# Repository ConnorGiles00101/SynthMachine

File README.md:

# SynthMachine
A set of Modular synthesizer modules designed around the SSI2130 VCO, SSI2140 Multi-Mode Filter, and the Daisy Seed Microcontroller.

Firmware requires a daisy seed build environment to compile, see daisy seed startup guide (https://daisy.audio/tutorials/cpp-dev-env/), requires updated libdaisy, daisysp, etc... to be cloned from relevant repos.

Very much a prototype.

Credit to timMJN and his Polymorph VCO module: https://github.com/TimMJN/Polymorph-VCO
His designs were helpful reference whilst learning modular synth i/o and standards regarding audio and CV voltage ranges and impedance.

VCO Machine and VCF Machine are designed to use the DAB2130 and DAB2140 breakout boards. As such they have DIP footprints instead of QFN, and do not have decoupling capacitors as they are already included on the breakout.

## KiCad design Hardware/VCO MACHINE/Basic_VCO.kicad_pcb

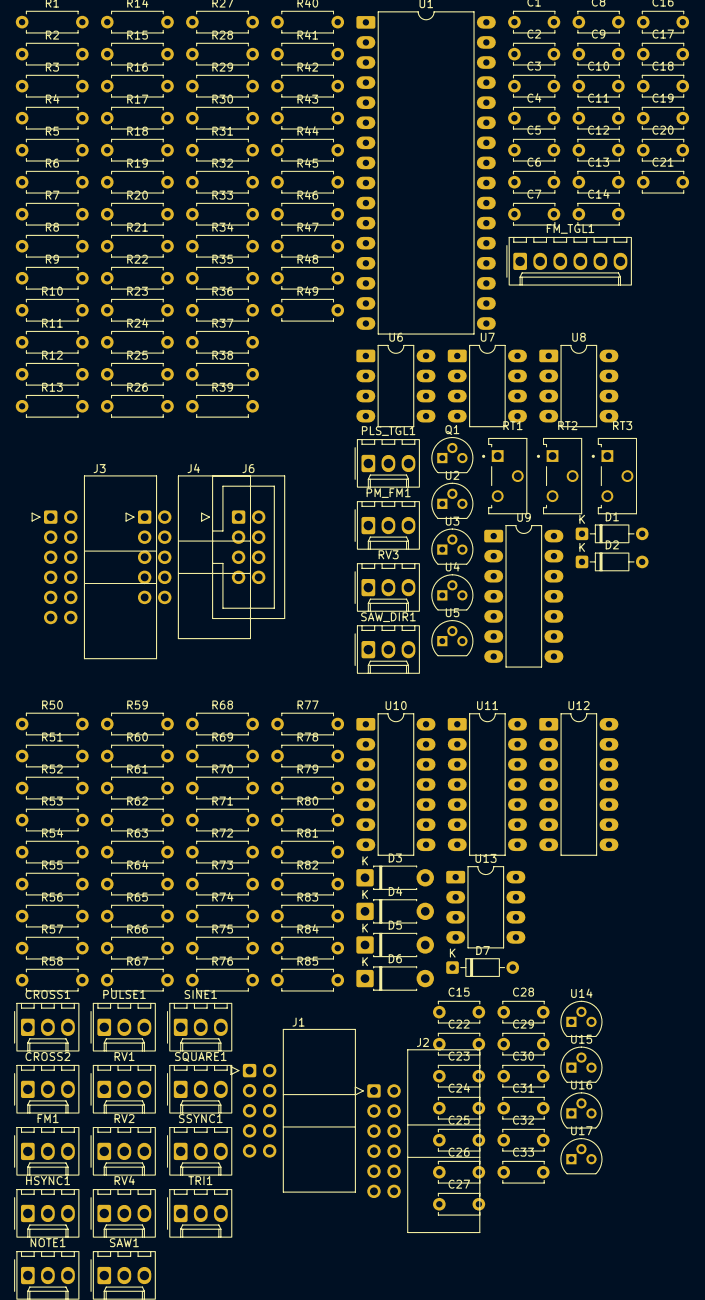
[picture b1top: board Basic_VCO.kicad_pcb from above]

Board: 4 copper layers, 170 parts (0 on the bottom side), 105 nets, no tracks yet.

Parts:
C1, C3, C30, C31: 0.33uF; C_Disc_D5.0mm_W2.5mm_P5.00mm
C2, C4, C12, C14, C16, C17, C18, C19, C20, C21, C22, C23, C24, C25, C26, C27, C28, C29, C32, C33: 0.1uF; C_Disc_D5.0mm_W2.5mm_P5.00mm
C5, C6, C8: 10nF; C_Disc_D5.0mm_W2.5mm_P5.00mm
C7: 3.9nF; C_Disc_D5.0mm_W2.5mm_P5.00mm
C9: 10uF; C_Disc_D5.0mm_W2.5mm_P5.00mm
C10, C11, C13, C15: 100pF; C_Disc_D5.0mm_W2.5mm_P5.00mm
CROSS1, CROSS2: AudioJack2_SwitchT; Molex_KK-254_AE-6410-03A_1x03_P2.54mm_Vertical
D1, D2, D7: 1N4148; D_DO-35_SOD27_P7.62mm_Horizontal
D3, D4, D5, D6: 1N5817; D_DO-41_SOD81_P7.62mm_Horizontal
FM1: AudioJack2_SwitchT; Molex_KK-254_AE-6410-03A_1x03_P2.54mm_Vertical
FM_TGL1: SW_DPDT_x2; Molex_KK-254_AE-6410-06A_1x06_P2.54mm_Vertical
HSYNC1: AudioJack2_SwitchT; Molex_KK-254_AE-6410-03A_1x03_P2.54mm_Vertical
J1, J4: Conn_02x05_Odd_Even; IDC-Header_2x05_P2.54mm_Horizontal
J2, J3: Conn_02x06_Odd_Even; IDC-Header_2x06_P2.54mm_Horizontal
J6: Conn_02x05_Odd_Even; IDC-Header_2x04_P2.54mm_Vertical
NOTE1: AudioJack2_SwitchT; Molex_KK-254_AE-6410-03A_1x03_P2.54mm_Vertical
PLS_TGL1: SW_SPDT; Molex_KK-254_AE-6410-03A_1x03_P2.54mm_Vertical
PM_FM1: SW_SPDT; Molex_KK-254_AE-6410-03A_1x03_P2.54mm_Vertical
PULSE1: AudioJack2_SwitchT; Molex_KK-254_AE-6410-03A_1x03_P2.54mm_Vertical
Q1: 2N7000; TO-92
R1, R3, R58, R83: 10; R_Axial_DIN0207_L6.3mm_D2.5mm_P7.62mm_Horizontal
R2, R4, R13, R84, R85: 267; R_Axial_DIN0207_L6.3mm_D2.5mm_P7.62mm_Horizontal
R5: 15k; R_Axial_DIN0207_L6.3mm_D2.5mm_P7.62mm_Horizontal
R6, R7, R10, R15, R26, R35, R37, R45, R47, R57, R59, R63, R67, R71, R75: 10k; R_Axial_DIN0207_L6.3mm_D2.5mm_P7.62mm_Horizontal
R8, R50, R51, R52, R53, R54, R55, R81, R82: 49.9k; R_Axial_DIN0207_L6.3mm_D2.5mm_P7.62mm_Horizontal
R9: 267k; R_Axial_DIN0207_L6.3mm_D2.5mm_P7.62mm_Horizontal
R11, R24, R25, R34: 100k; R_Axial_DIN0207_L6.3mm_D2.5mm_P7.62mm_Horizontal
R12: 22.1k; R_Axial_DIN0207_L6.3mm_D2.5mm_P7.62mm_Horizontal
R14, R16, R33: 100; R_Axial_DIN0207_L6.3mm_D2.5mm_P7.62mm_Horizontal
R17: 19.6k; R_Axial_DIN0207_L6.3mm_D2.5mm_P7.62mm_Horizontal
R18, R20: 4.75k; R_Axial_DIN0207_L6.3mm_D2.5mm_P7.62mm_Horizontal
R19: 4.02k; R_Axial_DIN0207_L6.3mm_D2.5mm_P7.62mm_Horizontal
R21: 12.7k; R_Axial_DIN0207_L6.3mm_D2.5mm_P7.62mm_Horizontal
R22, R23, R27, R28, R29, R30, R31, R32, R38, R39, R40, R41, R42, R43, R44, R46, R48, R49, R60, R64, R68, R72, R76, R78: 20k; R_Axial_DIN0207_L6.3mm_D2.5mm_P7.62mm_Horizontal
R36: 499k; R_Axial_DIN0207_L6.3mm_D2.5mm_P7.62mm_Horizontal
R56: 90.9k; R_Axial_DIN0207_L6.3mm_D2.5mm_P7.62mm_Horizontal
R61, R65, R69, R73: 40.2k; R_Axial_DIN0207_L6.3mm_D2.5mm_P7.62mm_Horizontal
R62, R66, R70, R74, R77, R79: 1k; R_Axial_DIN0207_L6.3mm_D2.5mm_P7.62mm_Horizontal
R80: 1M; R_Axial_DIN0207_L6.3mm_D2.5mm_P7.62mm_Horizontal
RT1, RT2, RT3: 5k; TRIM_PV36Y203C01B00
RV1, RV2, RV4: 100k; Molex_KK-254_AE-6410-03A_1x03_P2.54mm_Vertical
RV3: 5k; Molex_KK-254_AE-6410-03A_1x03_P2.54mm_Vertical
SAW1: AudioJack2_SwitchT; Molex_KK-254_AE-6410-03A_1x03_P2.54mm_Vertical
SAW_DIR1: SW_SPDT; Molex_KK-254_AE-6410-03A_1x03_P2.54mm_Vertical
SINE1: AudioJack2_SwitchT; Molex_KK-254_AE-6410-03A_1x03_P2.54mm_Vertical
SQUARE1: AudioJack2_SwitchT; Molex_KK-254_AE-6410-03A_1x03_P2.54mm_Vertical
SSYNC1: AudioJack2_SwitchT; Molex_KK-254_AE-6410-03A_1x03_P2.54mm_Vertical
TRI1: AudioJack2_SwitchT; Molex_KK-254_AE-6410-03A_1x03_P2.54mm_Vertical
U1: SSI2130; DIP-32_W15.24mm_LongPads
U2, U14: L78L05_TO92; TO-92
U3, U5, U16, U17: TL431LP; TO-92
U4, U15: L79L05_TO92; TO-92
U6, U7, U13: TL072; DIP-8_W7.62mm_LongPads
U8: LM311; DIP-8_W7.62mm_LongPads
U9, U10, U11, U12: TL074; DIP-14_W7.62mm_LongPads

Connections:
+2V5: D3.1 (K), D5.1 (K), FM_TGL1.1 (A), R2.2, R11.2, R12.1, R15.2, R21.2, R28.2, R84.2, RT1.3, U1.23 (VREF), U3.1 (REF), U3.3 (K), U16.1 (REF), U16.3 (K)
+5V: C2.1, C32.1, R2.1, R14.1, R22.2, R35.2, R84.1, RV2.3, SAW_DIR1.1 (A), U1.27 (V+), U2.1 (VO), U14.1 (VO)
+12V: C12.1, C17.1, C18.1, C20.1, C23.1, C24.1, C26.1, C28.1, J1.9, J1.10, J4.9, J4.10, R1.1, R58.1, U6.4 (V-), U7.4 (V-), U8.8 (V+), U9.11 (V-), U10.11 (V-), U11.11 (V-), U12.11 (V-), U13.8 (V+)
-1V0: R40.1, U6.1, U6.2 (-)
-2V5: R4.2, R5.1, R60.1, R64.1, R68.1, R72.1, R85.2, U5.2 (A), U17.2 (A)
-5V: C4.1, C33.1, R4.1, R85.1, U4.3 (VO), U15.3 (VO)
-12V: C14.2, C16.2, C19.2, C21.2, C22.2, C25.2, C27.2, C29.2, J1.1, J1.2, J4.1, J4.2, J6.1, J6.2, R3.1, R17.2, R83.1, U1.8 (V-), U6.8 (V+), U7.8 (V+), U8.4 (V-), U9.4 (V+), U10.4 (V+), U11.4 (V+), U12.4 (V+), U13.4 (V-)
CROSSFADE CV: J3.4, R37.1, R47.1
CROSSFADE IN: J2.4, U11.8, U11.9 (-)
GND: C1.2, C2.2, C3.2, C4.2, C7.2, C8.2, C12.2, C14.1, C16.1, C17.2, C18.2, C19.1, C20.2, C21.1, C22.1, C23.2, C24.2, C25.1, C26.2, C27.1, C28.2, C29.1, C30.2, C31.2, C32.2, C33.2, D4.2 (A), D6.2 (A), J1.3, J1.4, J1.5, J1.6, J1.7, J1.8, J2.2, J3.2, J4.3, J4.4, J4.5, J4.6, J4.7, J4.8, J6.3, J6.4, J6.5, J6.6, J6.7, J6.8, Q1.1 (S), R6.2, R7.1, R16.2, R18.2, R20.2, R23.1, R24.1, R25.1, R26.2, R33.1, R48.1, R51.2, R54.1, R57.1, R80.2, R82.2, RT1.1, RT2.1, RV1.1, RV2.1, RV4.1, SAW_DIR1.3 (C), U1.15 (DGND), U1.16 (AGND), U1.20 (HFT_BASE), U2.2 (GND), U3.2 (A), U4.1 (GND), U5.1 (REF), U5.3 (K), U6.5 (+), U7.3 (+), U8.1 (GND), U9.3 (+), U9.5 (+), U9.12 (+), U11.12 (+), U12.3 (+), U12.5 (+), U12.10 (+), U12.12 (+), U13.2 (-), U14.2 (GND), U15.1 (GND), U16.2 (A), U17.1 (REF), U17.3 (K)
HARD SYNC CV: C5.1, J3.6, R7.2
HARD SYNC IN: J2.6, U10.13 (-), U10.14
LIN FREQ IN: R36.2, U1.21 (LIN_FREQ)
MIX OUT: R26.1, U1.25 (MIX_OUT)
NOTE CV: J3.12, R8.1
NOTE IN: J2.12, U10.1, U10.2 (-)
unnamed: C8.1, R13.1
unnamed: C13.1, R34.2
unnamed: C15.2, R78.2, R79.1, U13.7
unnamed: D1.2 (A), D2.1 (K), U9.1
unnamed: D1.1 (K), R38.2, R39.1
unnamed: D2.2 (A), R41.2, R42.1
unnamed: D3.2 (A), D4.1 (K), R81.2, R82.1, U10.10 (+)
unnamed: D5.2 (A), D6.1 (K), R50.2, R51.1, U10.12 (+)
unnamed: D7.2 (A), U11.7
unnamed: D7.1 (K), RV4.3, U11.6 (-)
unnamed: FM_TGL1.2 (B), R36.1
unnamed: C11.2, FM_TGL1.3 (C), R32.2, U7.7
unnamed: FM_TGL1.4 (A), SAW_DIR1.2 (B)
unnamed: C13.2, FM_TGL1.6 (C), Q1.2 (G), R35.1, U8.7
unnamed: C9.2, PM_FM1.1 (A), R27.1
unnamed: C9.1, PM_FM1.3 (C)
unnamed: Q1.3 (D), R31.2, U7.5 (+)
unnamed: R9.1, RT2.2
unnamed: R10.1, RT1.2
unnamed: R12.2, RT3.2, RT3.3
unnamed: R14.2, R15.1, RV3.3
unnamed: R16.1, R17.1, RV3.1
unnamed: R43.2, R44.2, R45.2, U9.7
unnamed: R46.2, R49.1, U9.8
unnamed: R53.1, RV2.2
unnamed: R55.2, R56.1, U11.1
unnamed: R61.1, R62.2, U12.1
unnamed: R65.1, R66.2, U12.7
unnamed: R69.1, R70.2, U12.8
unnamed: R73.1, R74.2, U12.14
unnamed: R76.1, R77.2, U13.1
unnamed: R13.2, U1.26 (BW_COMP)
unnamed: R8.2, R9.2, R10.2, R11.1, U1.7 (EXPO_FREQ)
unnamed: RT3.1, U1.22 (EXPO_SCALE)
unnamed: C5.2, U1.17 (HARD_SYNC)
unnamed: RT2.3, U1.6 (HF_TRACK)
unnamed: C6.2, U1.19 (SOFT_SYNC)
unnamed: C7.1, U1.14 (TCAP)
unnamed: R18.1, R19.1, U1.2 (SINE_IN+)
unnamed: R20.1, R21.1, U1.3 (SINE_IN-)
unnamed: R24.2, U1.12 (AUX1_MIX)
unnamed: R25.2, U1.13 (AUX2_MIX)
unnamed: C1.1, R1.2, U2.3 (VI)
unnamed: C3.1, R3.2, U4.2 (VI)
unnamed: R5.2, R6.1, U6.3 (+)
unnamed: U6.6 (-), U6.7
unnamed: C10.1, R27.2, R28.1, R29.1, U7.2 (-)
unnamed: C11.1, R30.2, R32.1, U7.6 (-)
unnamed: R33.2, R34.1, U8.2 (+)
unnamed: C10.2, R29.2, R30.1, R31.1, U7.1, U8.3 (-)
unnamed: R37.2, R38.1, R40.2, R41.1, U9.2 (-)
unnamed: R42.2, R43.1, U9.6 (-)
unnamed: R47.2, R48.2, U9.10 (+)
unnamed: R45.1, R46.1, U9.9 (-)
unnamed: U9.13 (-), U9.14
unnamed: R80.1, U10.3 (+)
unnamed: RV1.2, U10.5 (+)
unnamed: R52.2, R53.2, U11.3 (+)
unnamed: R54.2, R55.1, U11.2 (-)
unnamed: R56.2, R57.2, U11.5 (+)
unnamed: RV4.2, U11.10 (+)
unnamed: U11.13 (-), U11.14
unnamed: R59.2, R60.2, R61.2, U12.2 (-)
unnamed: R63.2, R64.2, R65.2, U12.6 (-)
unnamed: R67.2, R68.2, R69.2, U12.9 (-)
unnamed: R71.2, R72.2, R73.2, U12.13 (-)
unnamed: R75.2, R76.2, U13.3 (+)
unnamed: C15.1, R78.1, U13.5 (+)
unnamed: C30.1, R58.2, U14.3 (VI)
unnamed: C31.1, R83.2, U15.2 (VI)
PM/FM CV: J3.10, PM_FM1.2 (B)
PM/FM IN: J2.10, U10.6 (-), U10.7
PULSE MIX: R44.1, U1.11 (PULSE_MIX)
PULSE OUT: J3.3, J3.7, U1.30 (PULSE_OUT)
PULSE WAVE: J2.3, J2.7, R71.1
PWM+: RV3.2, U1.32 (PWM+)
PWM-: PLS_TGL1.2 (B), U1.31 (PWM-)
SAW MIX: R49.2, U1.10 (SAW_MIX)
SAW OUT: J3.9, PLS_TGL1.3 (C), U1.29 (SAW_OUT)
SAW WAVE: J2.9, R63.1
SINE OUT: J3.1, U1.24 (SINE_OUT)
SINE WAVE: J2.1, R75.1
SOFT SYNC CV: C6.1, J3.8
SOFT SYNC IN: J2.8, U10.8, U10.9 (-)
SQUARE OUT: J3.5, R22.1, R23.2, U1.28 (SQUARE_OUT)
SQUARE WAVE: J2.5, R67.1
TIME REV IN: FM_TGL1.5 (B), U1.18 (TIME_REVERSE)
TRI MIX: R39.2, U1.9 (TRI_MIX)
TRI OUT: PLS_TGL1.1 (A), R19.2, U1.1 (TRI_OUT)

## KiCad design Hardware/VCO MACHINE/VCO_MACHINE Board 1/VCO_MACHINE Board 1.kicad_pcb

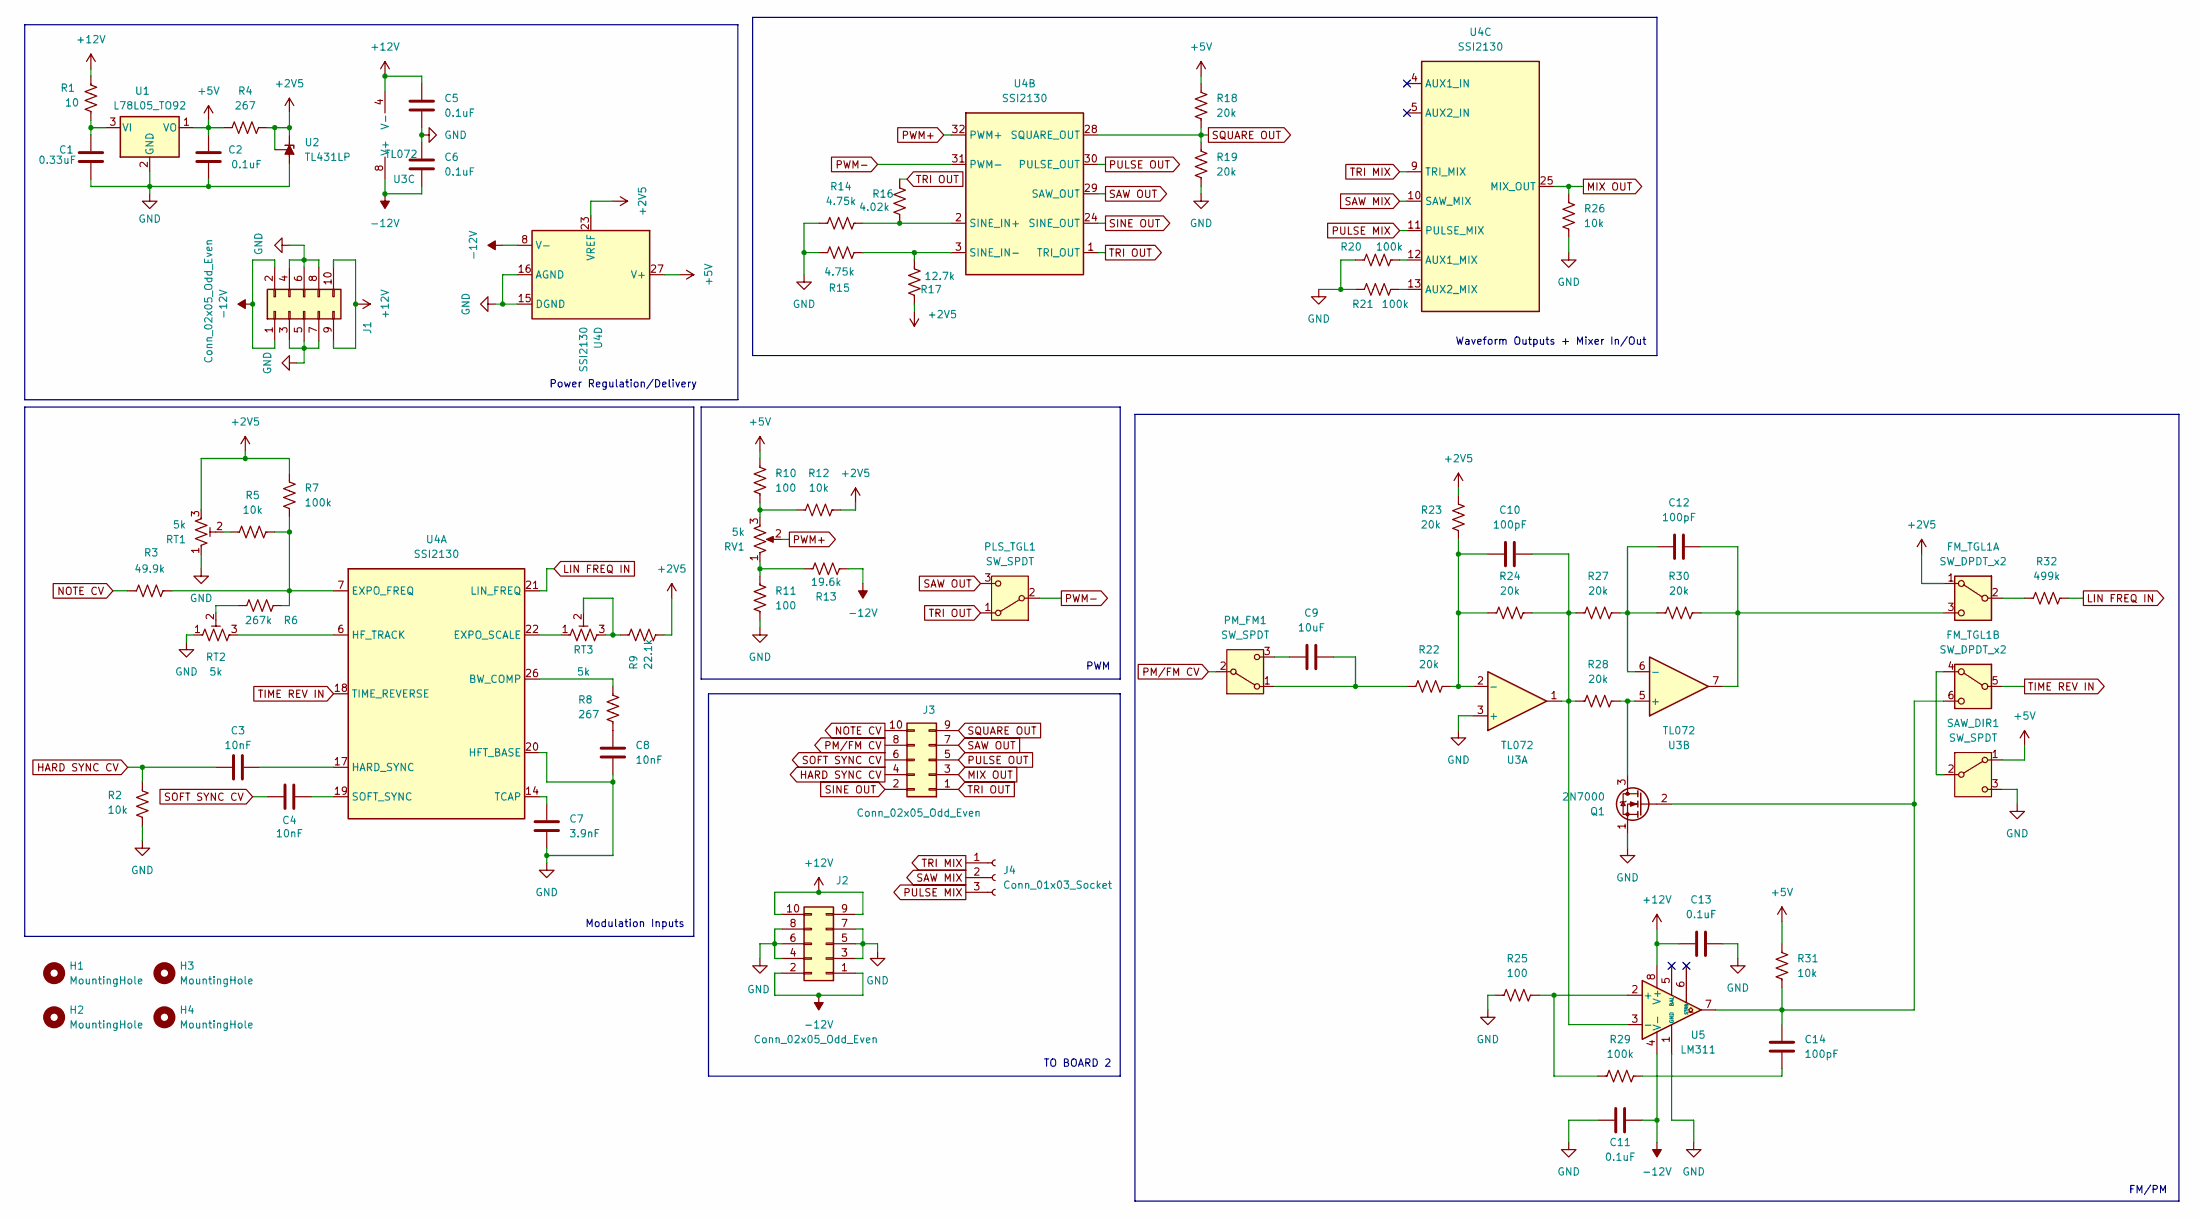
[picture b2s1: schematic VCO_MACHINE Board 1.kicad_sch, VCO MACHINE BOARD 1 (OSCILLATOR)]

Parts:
C1: 0.33uF; C_Disc_D5.0mm_W2.5mm_P5.00mm; LCSC C73142
C2, C5, C6, C11, C13: 0.1uF; C_Disc_D5.0mm_W2.5mm_P5.00mm; LCSC C307331
C3, C4, C8: 10nF; C_Disc_D5.0mm_W2.5mm_P5.00mm; LCSC C60133
C7: 3.9nF; C_Disc_D5.0mm_W2.5mm_P5.00mm; LCSC C326569
C9: 10uF; C_Disc_D5.0mm_W2.5mm_P5.00mm; LCSC C2932476
C10, C12, C14: 100pF; C_Disc_D5.0mm_W2.5mm_P5.00mm; LCSC C106200
FM_TGL1: SW_DPDT_x2; Molex_KK-254_1x06_P2.54mm_Horizontal
H1, H2, H3, H4: MountingHole; MountingHole_2.2mm_M2
J1: Conn_02x05_Odd_Even; IDC-Header_2x05_P2.54mm_Vertical
J2: Conn_02x05_Odd_Even; IDC-Header_2x06_P2.54mm_Horizontal
J3: Conn_02x05_Odd_Even; IDC-Header_2x05_P2.54mm_Horizontal
J4: Conn_01x03_Socket; Molex_KK-254_1x03_P2.54mm_Horizontal
PLS_TGL1: SW_SPDT; Molex_KK-254_1x03_P2.54mm_Horizontal
PM_FM1: SW_SPDT; Molex_KK-254_1x03_P2.54mm_Horizontal
Q1: 2N7000; TO-92; LCSC C8545
R1: 10; R_Axial_DIN0207_L6.3mm_D2.5mm_P7.62mm_Horizontal; LCSC C17903
R2, R5, R12, R26, R31: 10k; R_Axial_DIN0207_L6.3mm_D2.5mm_P7.62mm_Horizontal; LCSC C25744
R3: 49.9k; R_Axial_DIN0207_L6.3mm_D2.5mm_P7.62mm_Horizontal; LCSC C853300
R4, R8: 267; R_Axial_DIN0207_L6.3mm_D2.5mm_P7.62mm_Horizontal; LCSC C2974054
R6: 267k; R_Axial_DIN0207_L6.3mm_D2.5mm_P7.62mm_Horizontal; LCSC C4315442
R7, R20, R21, R29: 100k; R_Axial_DIN0207_L6.3mm_D2.5mm_P7.62mm_Horizontal; LCSC C852472
R9: 22.1k; R_Axial_DIN0207_L6.3mm_D2.5mm_P7.62mm_Horizontal; LCSC C852648
R10, R11, R25: 100; R_Axial_DIN0207_L6.3mm_D2.5mm_P7.62mm_Horizontal; LCSC C705627
R13: 19.6k; R_Axial_DIN0207_L6.3mm_D2.5mm_P7.62mm_Horizontal; LCSC C850848
R14, R15: 4.75k; R_Axial_DIN0207_L6.3mm_D2.5mm_P7.62mm_Horizontal; LCSC C854352
R16: 4.02k; R_Axial_DIN0207_L6.3mm_D2.5mm_P7.62mm_Horizontal; LCSC C852810
R17: 12.7k; R_Axial_DIN0207_L6.3mm_D2.5mm_P7.62mm_Horizontal; LCSC C852509
R18, R19, R22, R23, R24, R27, R28, R30: 20k; R_Axial_DIN0207_L6.3mm_D2.5mm_P7.62mm_Horizontal; LCSC C705630
R32: 499k; R_Axial_DIN0207_L6.3mm_D2.5mm_P7.62mm_Horizontal; LCSC C2074186
RT1, RT2, RT3: 5k; TRIM_PV36Y203C01B00
RV1: 5k; Molex_KK-254_1x03_P2.54mm_Horizontal
SAW_DIR1: SW_SPDT; Molex_KK-254_1x03_P2.54mm_Horizontal
U1: L78L05_TO92; TO-92; LCSC C42738
U2: TL431LP; TO-92; LCSC C18814
U3: TL072; DIP-8_W7.62mm_LongPads; LCSC C6962
U4: SSI2130; DIP-32_W15.24mm
U5: LM311; DIP-8_W7.62mm_LongPads; LCSC C12597

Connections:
+2V5: FM_TGL1.1 (A), R4.2, R7.2, R9.1, R12.2, R17.2, R23.2, RT1.3, U2.1 (REF), U2.3 (K), U4.23 (VREF)
+5V: C2.1, R4.1, R10.1, R18.2, R31.2, SAW_DIR1.1 (A), U1.1 (VO), U4.27 (V+)
+12V: C5.1, C13.1, J1.9, J1.10, J2.9, J2.10, R1.1, U3.4 (V-), U5.8 (V+)
-12V: C6.2, C11.2, J1.1, J1.2, J2.1, J2.2, R13.2, U3.8 (V+), U4.8 (V-), U5.4 (V-)
GND: C1.2, C2.2, C5.2, C6.1, C7.2, C8.2, C11.1, C13.2, J1.3, J1.4, J1.5, J1.6, J1.7, J1.8, J2.3, J2.4, J2.5, J2.6, J2.7, J2.8, Q1.1 (S), R2.1, R11.2, R14.2, R15.2, R19.1, R20.1, R21.1, R25.1, R26.2, RT1.1, RT2.1, SAW_DIR1.3 (C), U1.2 (GND), U2.2 (A), U3.3 (+), U4.15 (DGND), U4.16 (AGND), U4.20 (HFT_BASE), U5.1 (GND)
HARD SYNC CV: C3.1, J3.4, R2.2
LIN FREQ IN: R32.2, U4.21 (LIN_FREQ)
MIX OUT: J3.3, R26.1, U4.25 (MIX_OUT)
NOTE CV: J3.10, R3.1
unnamed: C8.1, R8.1
unnamed: C14.1, R29.2
unnamed: FM_TGL1.2 (B), R32.1
unnamed: C12.2, FM_TGL1.3 (C), R30.2, U3.7
unnamed: FM_TGL1.4 (A), SAW_DIR1.2 (B)
unnamed: C14.2, FM_TGL1.6 (C), Q1.2 (G), R31.1, U5.7
unnamed: C9.2, PM_FM1.1 (A), R22.1
unnamed: C9.1, PM_FM1.3 (C)
unnamed: Q1.3 (D), R28.2, U3.5 (+)
unnamed: R5.1, RT1.2
unnamed: R6.1, RT2.2
unnamed: R9.2, RT3.2, RT3.3
unnamed: R10.2, R12.1, RV1.3
unnamed: R11.1, R13.1, RV1.1
unnamed: C1.1, R1.2, U1.3 (VI)
unnamed: C10.1, R22.2, R23.1, R24.1, U3.2 (-)
unnamed: C12.1, R27.2, R30.1, U3.6 (-)
unnamed: R8.2, U4.26 (BW_COMP)
unnamed: R3.2, R5.2, R6.2, R7.1, U4.7 (EXPO_FREQ)
unnamed: RT3.1, U4.22 (EXPO_SCALE)
unnamed: C3.2, U4.17 (HARD_SYNC)
unnamed: RT2.3, U4.6 (HF_TRACK)
unnamed: C4.2, U4.19 (SOFT_SYNC)
unnamed: C7.1, U4.14 (TCAP)
unnamed: R14.1, R16.1, U4.2 (SINE_IN+)
unnamed: R15.1, R17.1, U4.3 (SINE_IN-)
unnamed: R20.2, U4.12 (AUX1_MIX)
unnamed: R21.2, U4.13 (AUX2_MIX)
unnamed: R25.2, R29.1, U5.2 (+)
unnamed: C10.2, R24.2, R27.1, R28.1, U3.1, U5.3 (-)
PM/FM CV: J3.8, PM_FM1.2 (B)
PULSE MIX: J4.3, U4.11 (PULSE_MIX)
PULSE OUT: J3.5, U4.30 (PULSE_OUT)
PWM+: RV1.2, U4.32 (PWM+)
PWM-: PLS_TGL1.2 (B), U4.31 (PWM-)
SAW MIX: J4.2, U4.10 (SAW_MIX)
SAW OUT: J3.7, PLS_TGL1.3 (C), U4.29 (SAW_OUT)
SINE OUT: J3.2, U4.24 (SINE_OUT)
SOFT SYNC CV: C4.1, J3.6
SQUARE OUT: J3.9, R18.1, R19.2, U4.28 (SQUARE_OUT)
TIME REV IN: FM_TGL1.5 (B), U4.18 (TIME_REVERSE)
TRI MIX: J4.1, U4.9 (TRI_MIX)
TRI OUT: J3.1, PLS_TGL1.1 (A), R16.2, U4.1 (TRI_OUT)

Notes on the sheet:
Waveform Outputs + Mixer In/Out
FM/PM
Modulation Inputs
TO BOARD 2
PWM
Power Regulation/Delivery

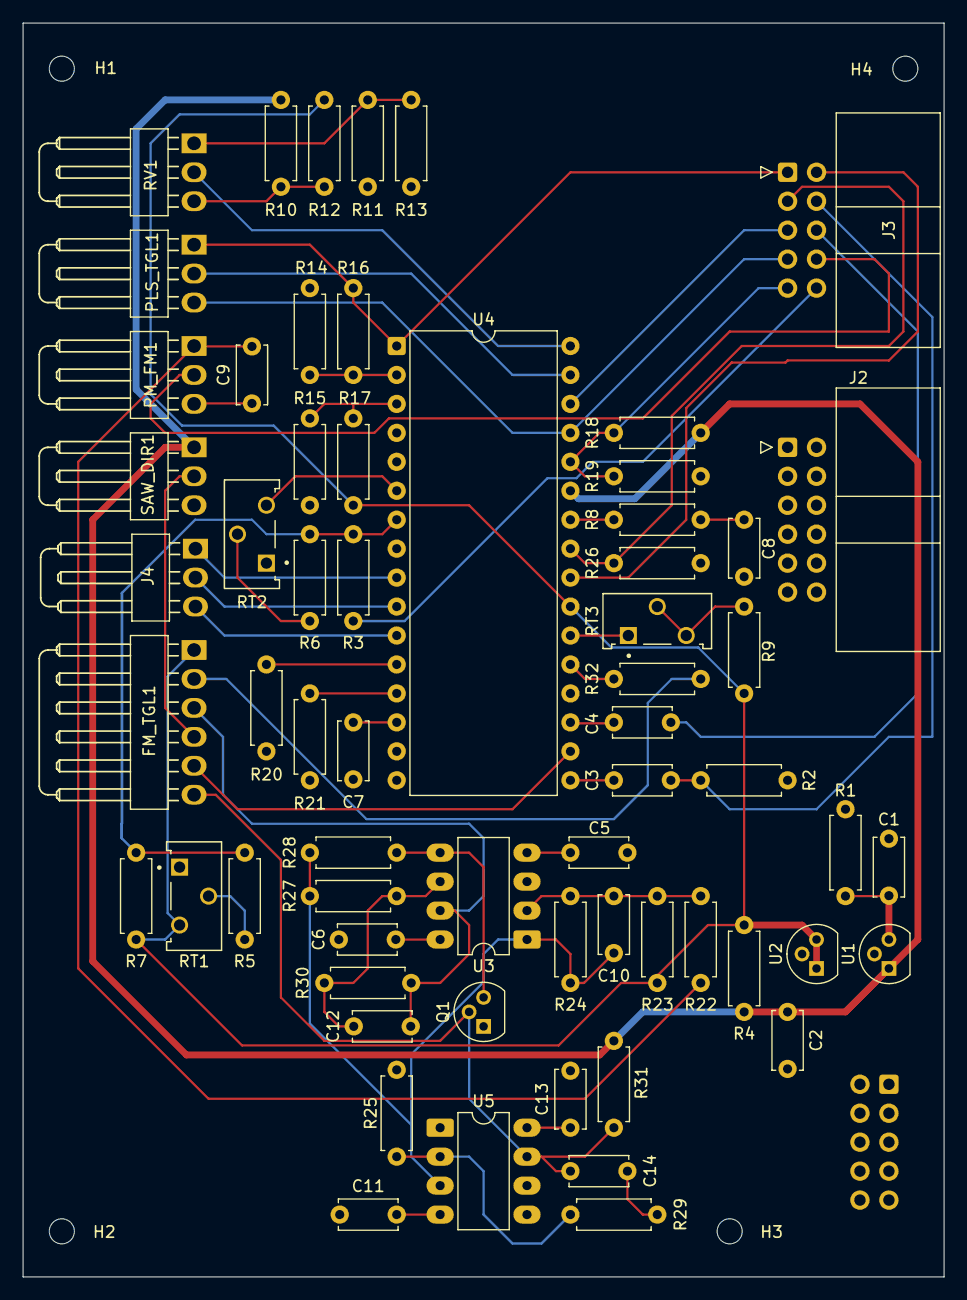
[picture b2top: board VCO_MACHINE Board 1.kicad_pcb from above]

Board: 4 copper layers, 80.8 x 110.0 mm, 68 parts (1 on the bottom side), 52 nets.

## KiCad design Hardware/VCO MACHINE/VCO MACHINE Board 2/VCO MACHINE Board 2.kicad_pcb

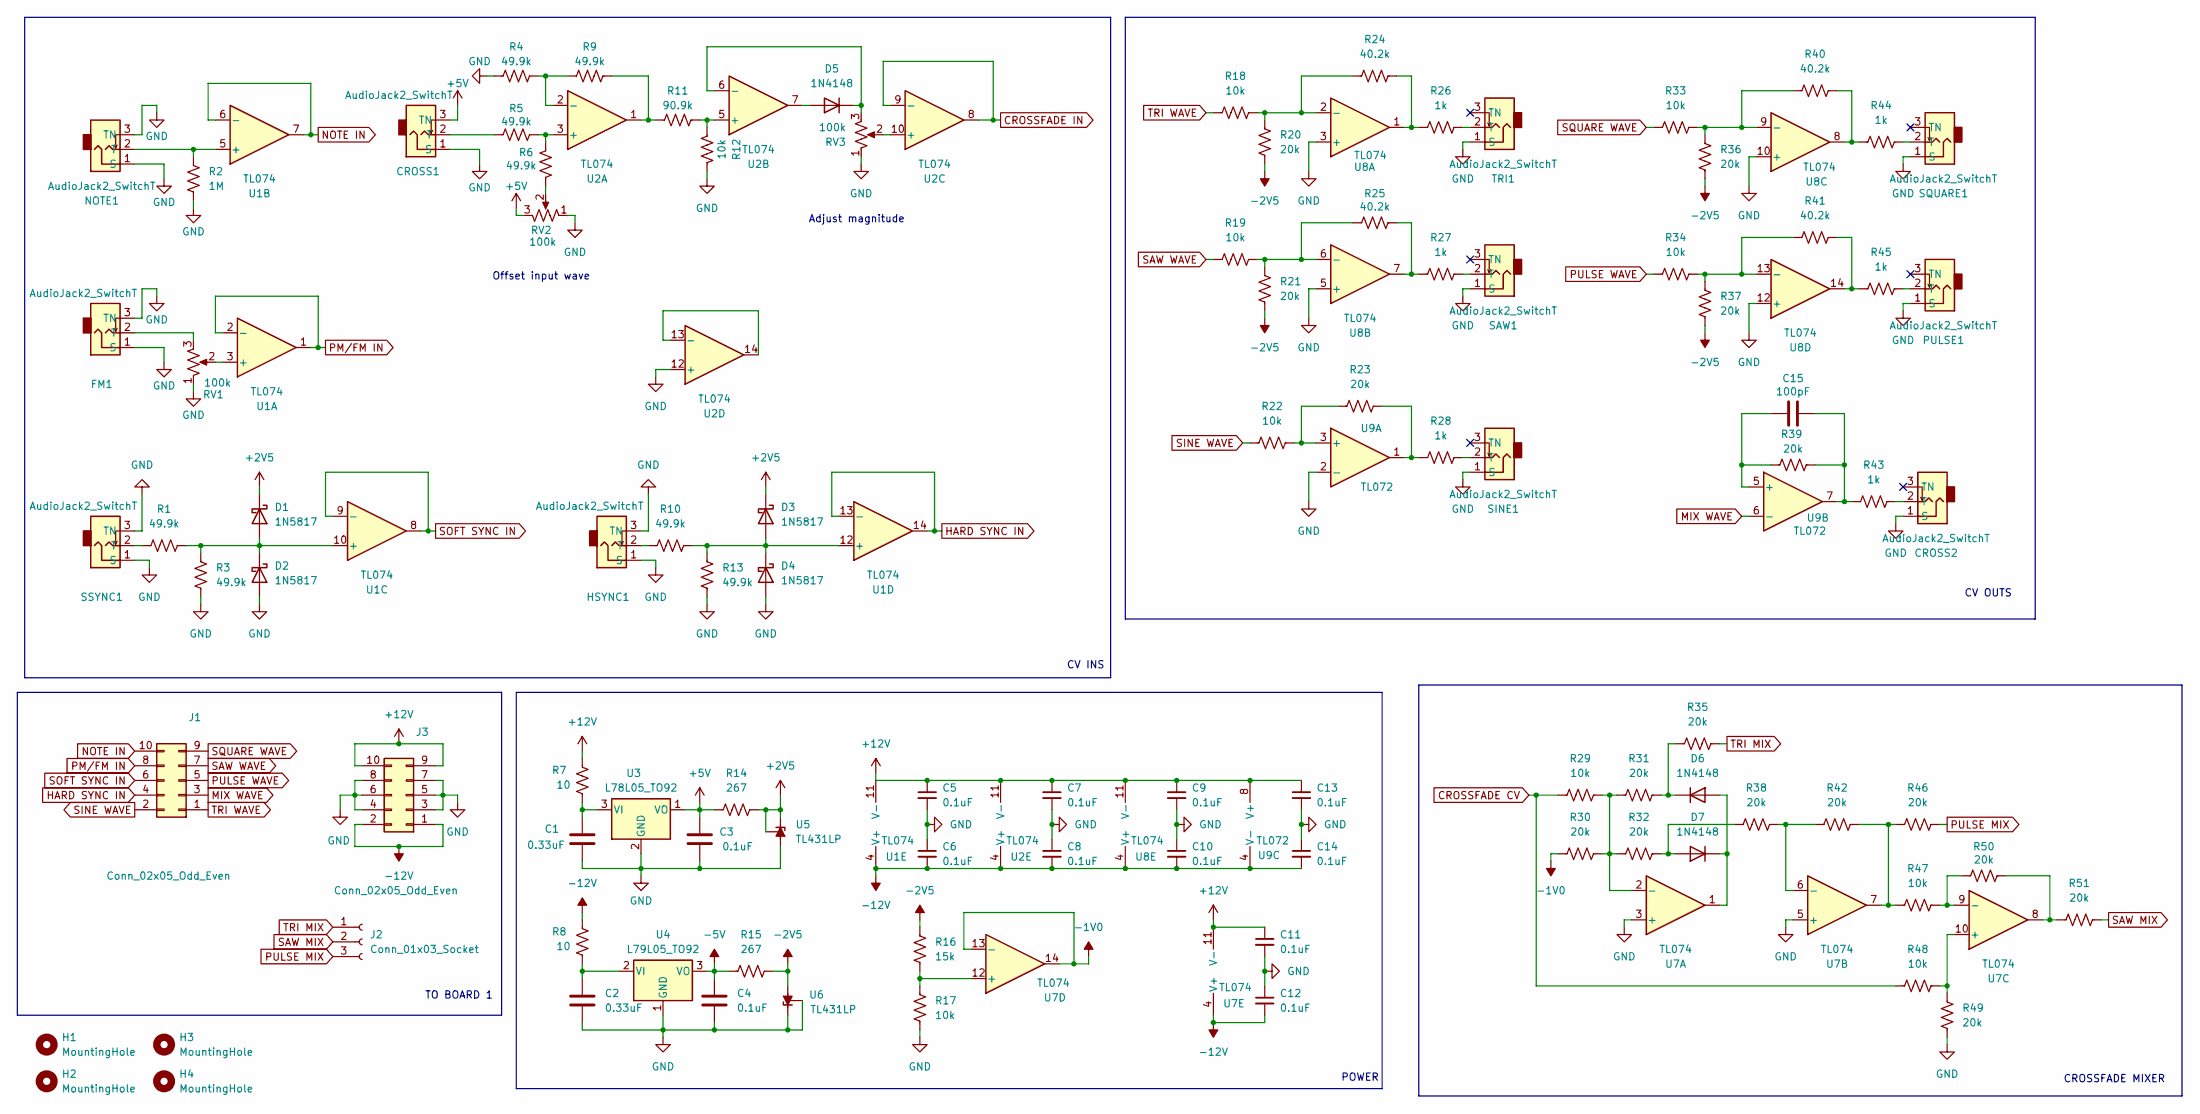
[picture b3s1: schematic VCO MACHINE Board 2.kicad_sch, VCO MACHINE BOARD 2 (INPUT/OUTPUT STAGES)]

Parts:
C1, C2: 0.33uF; C_Disc_D5.0mm_W2.5mm_P5.00mm; LCSC C73142
C3, C4: 0.1uF; C_Disc_D5.0mm_W2.5mm_P5.00mm; LCSC C307331
C5, C6, C7, C8, C9, C10, C11, C12, C13, C14: 0.1uF; C_Disc_D5.0mm_W2.5mm_P5.00mm
C15: 100pF; C_Disc_D5.0mm_W2.5mm_P5.00mm; LCSC C106200
CROSS1, CROSS2: AudioJack2_SwitchT; Molex_KK-254_1x03_P2.54mm_Horizontal
D1, D2, D3, D4: 1N5817; D_DO-41_SOD81_P7.62mm_Horizontal; LCSC C727113
D5, D6, D7: 1N4148; D_DO-35_SOD27_P7.62mm_Horizontal; LCSC C81598
FM1: AudioJack2_SwitchT; Molex_KK-254_1x03_P2.54mm_Horizontal
H1, H2, H3, H4: MountingHole; MountingHole_2.2mm_M2
HSYNC1: AudioJack2_SwitchT; Molex_KK-254_1x03_P2.54mm_Horizontal
J1: Conn_02x05_Odd_Even; IDC-Header_2x05_P2.54mm_Horizontal
J2: Conn_01x03_Socket; IDC-Header_2x05_P2.54mm_Horizontal
J3: Conn_02x05_Odd_Even; Molex_KK-254_1x03_P2.54mm_Horizontal
NOTE1: AudioJack2_SwitchT; Molex_KK-254_1x03_P2.54mm_Horizontal
PULSE1: AudioJack2_SwitchT; Molex_KK-254_1x03_P2.54mm_Horizontal
R1, R3, R4, R5, R6, R9, R10, R13: 49.9k; R_Axial_DIN0207_L6.3mm_D2.5mm_P7.62mm_Horizontal; LCSC C853300
R2: 1M; R_Axial_DIN0207_L6.3mm_D2.5mm_P7.62mm_Horizontal; LCSC C1884615
R7, R8: 10; R_Axial_DIN0207_L6.3mm_D2.5mm_P7.62mm_Horizontal; LCSC C17903
R11: 90.9k; R_Axial_DIN0207_L6.3mm_D2.5mm_P7.62mm_Horizontal; LCSC C854454
R12, R17, R18, R19, R22, R29, R33, R34, R47, R48: 10k; R_Axial_DIN0207_L6.3mm_D2.5mm_P7.62mm_Horizontal; LCSC C25744
R14, R15: 267; R_Axial_DIN0207_L6.3mm_D2.5mm_P7.62mm_Horizontal; LCSC C2974054
R16: 15k; R_Axial_DIN0207_L6.3mm_D2.5mm_P7.62mm_Horizontal; LCSC C25756
R20, R21, R23, R30, R31, R32, R35, R36, R37, R38, R39, R42, R46, R49, R50, R51: 20k; R_Axial_DIN0207_L6.3mm_D2.5mm_P7.62mm_Horizontal; LCSC C705630
R24, R25, R40, R41: 40.2k; R_Axial_DIN0207_L6.3mm_D2.5mm_P7.62mm_Horizontal; LCSC C852775
R26, R27, R28, R43, R44, R45: 1k; R_Axial_DIN0207_L6.3mm_D2.5mm_P7.62mm_Horizontal; LCSC C706405
RV1, RV2, RV3: 100k; Molex_KK-254_1x03_P2.54mm_Horizontal
SAW1: AudioJack2_SwitchT; Molex_KK-254_1x03_P2.54mm_Horizontal
SINE1: AudioJack2_SwitchT; Molex_KK-254_1x03_P2.54mm_Horizontal
SQUARE1: AudioJack2_SwitchT; Molex_KK-254_1x03_P2.54mm_Horizontal
SSYNC1: AudioJack2_SwitchT; Molex_KK-254_1x03_P2.54mm_Horizontal
TRI1: AudioJack2_SwitchT; Molex_KK-254_1x03_P2.54mm_Horizontal
U1, U2, U7, U8: TL074; DIP-14_W7.62mm_LongPads; LCSC C6964
U3: L78L05_TO92; TO-92; LCSC C42738
U4: L79L05_TO92; TO-92
U5, U6: TL431LP; TO-92; LCSC C18814
U9: TL072; DIP-8_W7.62mm_LongPads; LCSC C6962

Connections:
+2V5: D1.1 (K), D3.1 (K), R14.2, U5.1 (REF), U5.3 (K)
+5V: C3.1, CROSS1.3 (TN), R14.1, RV2.3, U3.1 (VO)
+12V: C5.1, C7.1, C9.1, C11.1, C13.1, J3.9, J3.10, R7.1, U1.11 (V-), U2.11 (V-), U7.11 (V-), U8.11 (V-), U9.8 (V+)
-1V0: R30.1, U7.13 (-), U7.14
-2V5: R15.2, R16.1, R20.1, R21.1, R36.1, R37.1, U6.2 (A)
-5V: C4.1, R15.1, U4.3 (VO)
-12V: C6.2, C8.2, C10.2, C12.2, C14.2, J3.1, J3.2, R8.1, U1.4 (V+), U2.4 (V+), U7.4 (V+), U8.4 (V+), U9.4 (V-)
CROSSFADE CV: R29.1, R48.1
CROSSFADE IN: U2.8, U2.9 (-)
GND: C1.2, C2.2, C3.2, C4.2, C5.2, C6.1, C7.2, C8.1, C9.2, C10.1, C11.2, C12.1, C13.2, C14.1, CROSS1.1 (S), CROSS2.1 (S), D2.2 (A), D4.2 (A), FM1.1 (S), FM1.3 (TN), HSYNC1.1 (S), HSYNC1.3 (TN), J3.3, J3.4, J3.5, J3.6, J3.7, J3.8, NOTE1.1 (S), NOTE1.3 (TN), PULSE1.1 (S), R2.2, R3.2, R4.1, R12.1, R13.2, R17.2, R49.1, RV1.1, RV2.1, RV3.1, SAW1.1 (S), SINE1.1 (S), SQUARE1.1 (S), SSYNC1.1 (S), SSYNC1.3 (TN), TRI1.1 (S), U2.12 (+), U3.2 (GND), U4.1 (GND), U5.2 (A), U6.1 (REF), U6.3 (K), U7.3 (+), U7.5 (+), U8.3 (+), U8.5 (+), U8.10 (+), U8.12 (+), U9.2 (-)
HARD SYNC IN: J1.4, U1.13 (-), U1.14
MIX WAVE: J1.3, U9.6 (-)
NOTE IN: J1.10, U1.6 (-), U1.7
unnamed: C15.2, R39.2, R43.1, U9.7
unnamed: CROSS1.2 (T), R5.1
unnamed: CROSS2.2 (T), R43.2
unnamed: D1.2 (A), D2.1 (K), R1.2, R3.1, U1.10 (+)
unnamed: D3.2 (A), D4.1 (K), R10.2, R13.1, U1.12 (+)
unnamed: D5.2 (A), U2.7
unnamed: D5.1 (K), RV3.3, U2.6 (-)
unnamed: D6.2 (A), D7.1 (K), U7.1
unnamed: D6.1 (K), R31.2, R35.1
unnamed: D7.2 (A), R32.2, R38.1
unnamed: FM1.2 (T), RV1.3
unnamed: HSYNC1.2 (T), R10.1
unnamed: NOTE1.2 (T), R2.1, U1.5 (+)
unnamed: PULSE1.2 (T), R45.1
unnamed: R6.1, RV2.2
unnamed: R9.2, R11.1, U2.1
unnamed: R23.1, R28.2, U9.1
unnamed: R24.1, R26.2, U8.1
unnamed: R25.1, R27.2, U8.7
unnamed: R40.1, R44.2, U8.8
unnamed: R41.1, R45.2, U8.14
unnamed: R42.2, R46.2, R47.2, U7.7
unnamed: R50.2, R51.1, U7.8
unnamed: R27.1, SAW1.2 (T)
unnamed: R28.1, SINE1.2 (T)
unnamed: R44.1, SQUARE1.2 (T)
unnamed: R1.1, SSYNC1.2 (T)
unnamed: R26.1, TRI1.2 (T)
unnamed: RV1.2, U1.3 (+)
unnamed: R5.2, R6.2, U2.3 (+)
unnamed: R4.2, R9.1, U2.2 (-)
unnamed: R11.2, R12.2, U2.5 (+)
unnamed: RV3.2, U2.10 (+)
unnamed: U2.13 (-), U2.14
unnamed: C1.1, R7.2, U3.3 (VI)
unnamed: C2.1, R8.2, U4.2 (VI)
unnamed: R29.2, R30.2, R31.1, R32.1, U7.2 (-)
unnamed: R38.2, R42.1, U7.6 (-)
unnamed: R48.2, R49.2, U7.10 (+)
unnamed: R47.1, R50.1, U7.9 (-)
unnamed: R16.2, R17.1, U7.12 (+)
unnamed: R18.2, R20.2, R24.2, U8.2 (-)
unnamed: R19.2, R21.2, R25.2, U8.6 (-)
unnamed: R33.2, R36.2, R40.2, U8.9 (-)
unnamed: R34.2, R37.2, R41.2, U8.13 (-)
unnamed: R22.2, R23.2, U9.3 (+)
unnamed: C15.1, R39.1, U9.5 (+)
PM/FM IN: J1.8, U1.1, U1.2 (-)
PULSE MIX: J2.3, R46.1
PULSE WAVE: J1.5, R34.1
SAW MIX: J2.2, R51.2
SAW WAVE: J1.7, R19.1
SINE WAVE: J1.2, R22.1
SOFT SYNC IN: J1.6, U1.8, U1.9 (-)
SQUARE WAVE: J1.9, R33.1
TRI MIX: J2.1, R35.2
TRI WAVE: J1.1, R18.1

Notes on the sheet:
CV INS
CROSSFADE MIXER
Offset input wave
Adjust magnitude
TO BOARD 1
POWER
CV OUTS

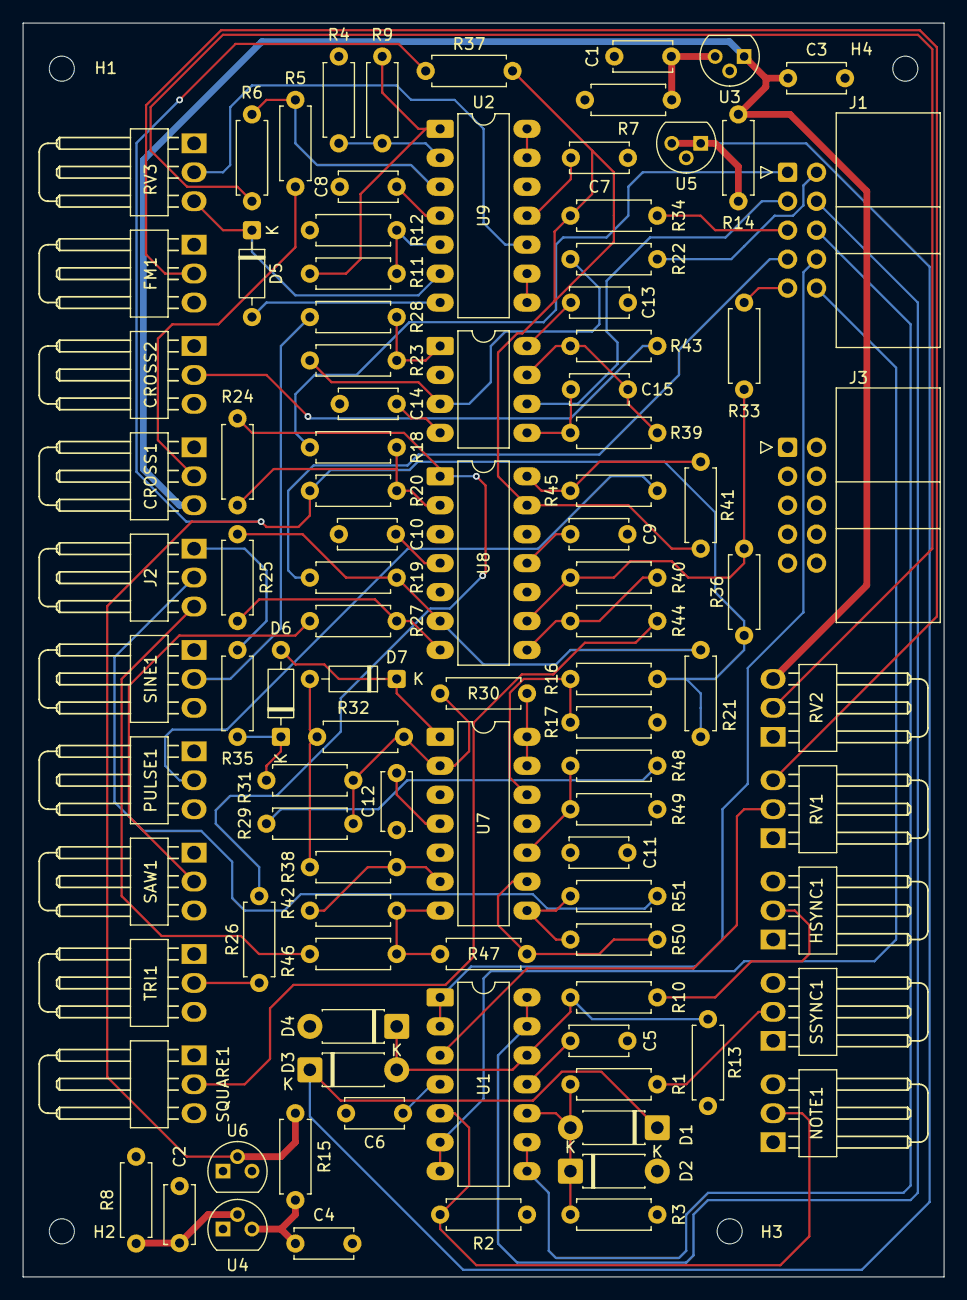
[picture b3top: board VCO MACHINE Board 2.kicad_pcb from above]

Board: 4 copper layers, 80.8 x 110.0 mm, 103 parts (0 on the bottom side), 70 nets.

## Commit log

2026-02-12 Added Initial KiCAD files
2026-02-12 deleted: SynthMachine.kicad_pcb deleted: SynthMachine.kicad_pro deleted: SynthMachine.kicad_sch
2026-02-12 new file: Hardware/Basic_VCO/Basic_VCO/Basic_VCO.kicad_pcb new file: Hardware/Basic_VCO/Basic_VCO/Basic_VCO.kicad_pro new file: Hardware/Basic_VCO/Basic_VCO/Basic_VCO.kicad_sch
2026-02-12 renamed: Hardware/Basic_VCO/Basic_VCO/Basic_VCO.kicad_pcb -> Hardware/Basic_VCO/Basic_VCO.kicad_pcb new file: Hardware/Basic_VCO/Basic_VCO.kicad_pro renamed: Hardware/Basic_VCO/Basic_VCO/Basic_VCO.ki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
2026-02-12 Initial Design Work - Test
2026-02-13 modified: Hardware/Basic_VCO/Basic_VCO.kicad_sch
2026-02-20 Added Daisy Seed Firmware, currently just here for reference, need to fix build environment.
2026-02-20 Revise comments in SYNTHMACHINE.cpp
    Revised comments to add some clarity.
2026-02-20 Additional comments added to SYNTHMACHINE.cpp
2026-02-20 Updated Basic VCO schematic, still missing inputs, and mixer controls.
2026-02-20 Added Initial Schematic for controller board using daisy seed for midi to cv and envelope controls
2026-02-26 Additional work to VCO schematic
2026-02-28 Finished 1st revision schematic for Basic VCO
2026-02-28 set some pcb footprints
2026-02-28 Changed Crossfade CV input to have 5V when disconnected instead of ground.
    Previously the Crossfade CV input would be grounded when disconnected from a CV source. now it is 5V allowing it to be set statically using offset and magnitude. CV input was designed expecting 10Vp-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
2026-03-04 adjusted schematic and prepared footprints for pcb design
2026-03-08 Re-organized, Basic VCO is now VCO MACHINE.
    Completed first version of PCBs, Basic VCO has been renamed to VCO MACHINE and redesigned to be split across two PCBs, connected via IDC, with Molex KK connectors for panel mount components.
